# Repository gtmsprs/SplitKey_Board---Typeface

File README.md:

# PROJECT_TYPEFACE
Keyboard based on the designs by @koeg - https://stasis.hackclub.com/starter-projects/split-keyboard

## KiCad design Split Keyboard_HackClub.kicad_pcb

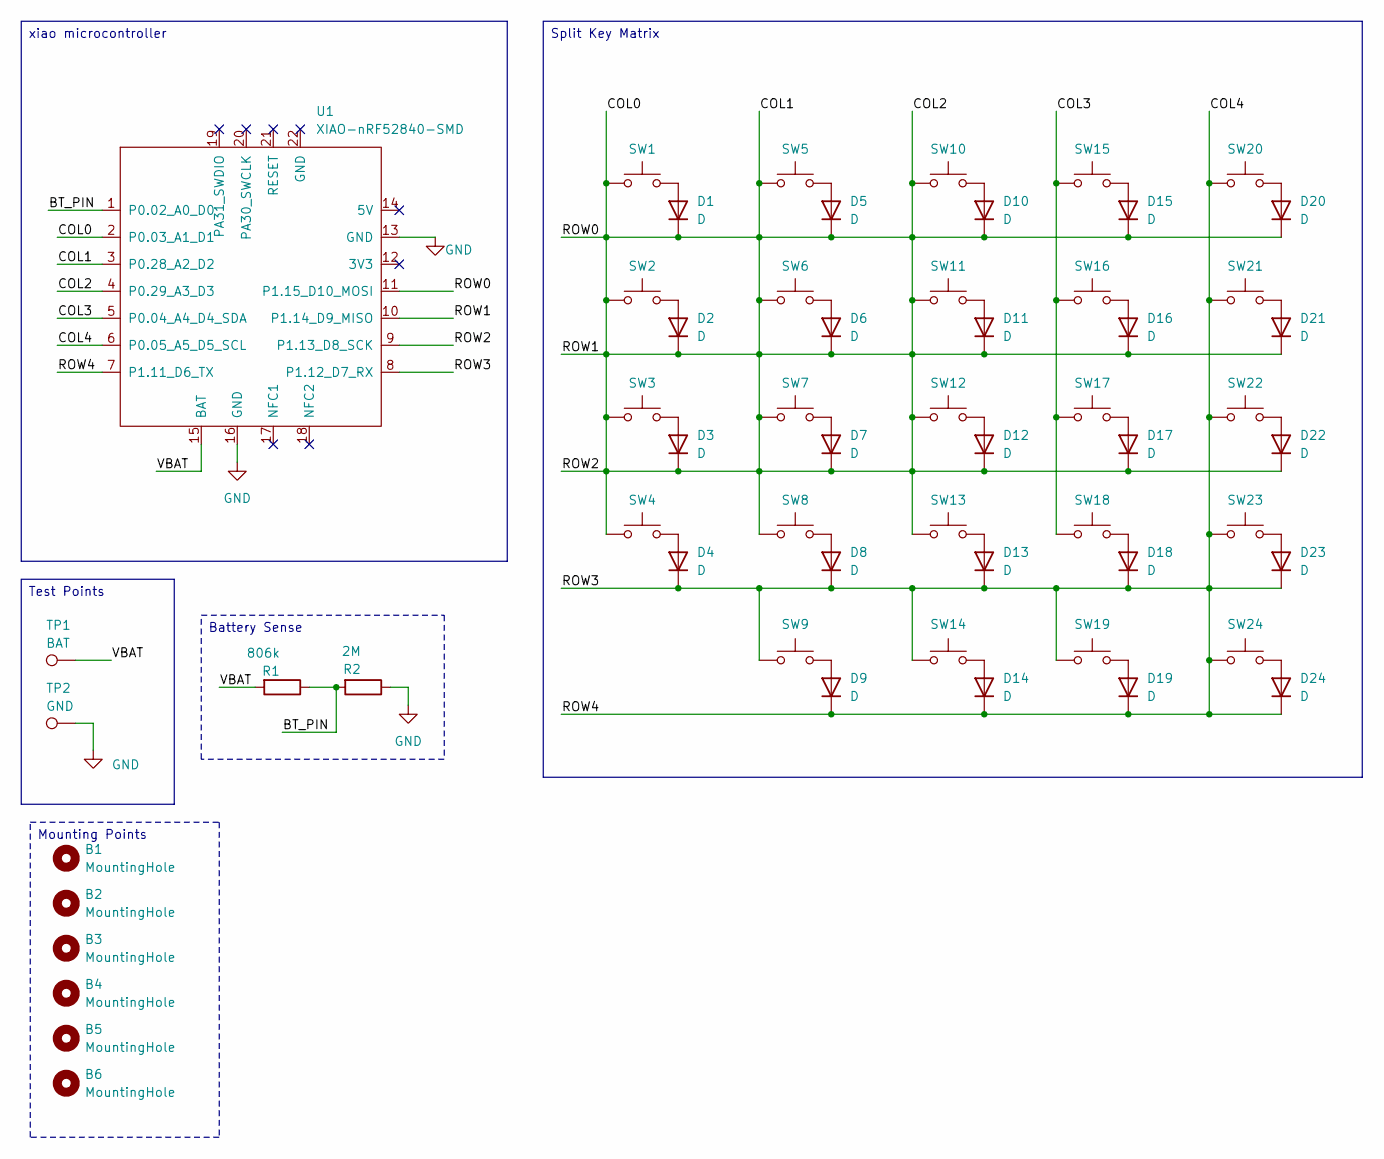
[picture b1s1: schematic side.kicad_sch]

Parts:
B1, B2, B3, B4, B5, B6: MountingHole
D1, D2, D3, D4, D5, D6, D7, D8, D9, D10, D11, D12, D13, D14, D15, D16, D17, D18, D19, D20, D21, D22, D23, D24: D; D_SMA
R1: 806k; R_0805_2012Metric
R2: 2M; R_0805_2012Metric
SW1, SW2, SW3, SW4, SW5, SW6, SW7, SW8, SW9, SW10, SW11, SW12, SW13, SW14, SW15, SW16, SW17, SW18, SW19, SW20, SW21, SW22, SW23, SW24: SW_Push; SW_KS33_HS_KS-2P02B01-02_HS_1u
TP1: BAT; TestPoint_Pad_D2.0mm
TP2: GND; TestPoint_Pad_D2.0mm
U1: XIAO-nRF52840-SMD; MCU_Seeed_ESP32C3

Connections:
/lefty/BT_PIN: R1.1, R2.2, U1.1 (P0.02_A0_D0)
/lefty/COL0: D1.1 (K), D2.1 (K), D3.1 (K), D5.1 (K), D6.1 (K), D7.1 (K), D10.1 (K), D11.1 (K), D12.1 (K), D15.1 (K), D16.1 (K), D17.1 (K), D20.1 (K), D21.1 (K), D22.1 (K), SW1.1, SW2.1, SW3.1, SW4.1, SW5.1, SW6.1, SW7.1, SW8.1, SW10.1, SW11.1, SW12.1, SW13.1, U1.2 (P0.03_A1_D1), U1.3 (P0.28_A2_D2), U1.4 (P0.29_A3_D3), U1.9 (P1.13_D8_SCK), U1.10 (P1.14_D9_MISO), U1.11 (P1.15_D10_MOSI)
/lefty/COL3: SW15.1, SW16.1, SW17.1, SW18.1, U1.5 (P0.04_A4_D4_SDA)
/lefty/COL4: D4.1 (K), D8.1 (K), D9.1 (K), D13.1 (K), D14.1 (K), D18.1 (K), D19.1 (K), D23.1 (K), D24.1 (K), SW9.1, SW14.1, SW19.1, SW20.1, SW21.1, SW22.1, SW23.1, SW24.1, U1.6 (P0.05_A5_D5_SCL), U1.7 (P1.11_D6_TX), U1.8 (P1.12_D7_RX)
/lefty/VBAT: R1.2, TP1.1 (1_1), U1.15 (BAT)
GND: R2.1, TP2.1 (1_1), U1.13 (GND), U1.16 (GND); also elsewhere on the board
unnamed: D1.2 (A), SW1.2
unnamed: D2.2 (A), SW2.2
unnamed: D3.2 (A), SW3.2
unnamed: D4.2 (A), SW4.2
unnamed: D5.2 (A), SW5.2
unnamed: D6.2 (A), SW6.2
unnamed: D7.2 (A), SW7.2
unnamed: D8.2 (A), SW8.2
unnamed: D9.2 (A), SW9.2
unnamed: D10.2 (A), SW10.2
unnamed: D11.2 (A), SW11.2
unnamed: D12.2 (A), SW12.2
unnamed: D13.2 (A), SW13.2
unnamed: D14.2 (A), SW14.2
unnamed: D15.2 (A), SW15.2
unnamed: D16.2 (A), SW16.2
unnamed: D17.2 (A), SW17.2
unnamed: D18.2 (A), SW18.2
unnamed: D19.2 (A), SW19.2
unnamed: D20.2 (A), SW20.2
unnamed: D21.2 (A), SW21.2
unnamed: D22.2 (A), SW22.2
unnamed: D23.2 (A), SW23.2
unnamed: D24.2 (A), SW24.2

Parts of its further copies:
D25, D26, D27, D28, D29, D30, D31, D32, D33, D34, D35, D36, D37, D38, D39, D40, D41, D42, D43, D44, D45, D46, D47, D48: D; D_SMA
R3: 806k; R_0805_2012Metric
R4: 2M; R_0805_2012Metric
SW25, SW26, SW27, SW28, SW29, SW30, SW31, SW32, SW33, SW34, SW35, SW36, SW37, SW38, SW39, SW40, SW41, SW42, SW43, SW44, SW45, SW46, SW47, SW48: SW_Push; SW_KS33_HS_KS-2P02B01-02_HS_1u
TP3: BAT; TestPoint_Pad_D2.0mm
TP4: GND; TestPoint_Pad_D2.0mm
U2: XIAO-nRF52840-SMD; MCU_Seeed_ESP32C3

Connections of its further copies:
/righty/BT_PIN: R3.1, R4.2, U2.1 (P0.02_A0_D0)
/righty/COL0: D25.1 (K), D26.1 (K), D27.1 (K), D29.1 (K), D30.1 (K), D31.1 (K), D34.1 (K), D35.1 (K), D36.1 (K), D39.1 (K), D40.1 (K), D41.1 (K), D44.1 (K), D45.1 (K), D46.1 (K), SW25.1, SW26.1, SW27.1, SW28.1, SW29.1, SW30.1, SW31.1, SW32.1, SW34.1, SW35.1, SW36.1, SW37.1, U2.2 (P0.03_A1_D1), U2.3 (P0.28_A2_D2), U2.4 (P0.29_A3_D3), U2.9 (P1.13_D8_SCK), U2.10 (P1.14_D9_MISO), U2.11 (P1.15_D10_MOSI)
/righty/COL3: SW39.1, SW40.1, SW41.1, SW42.1, U2.5 (P0.04_A4_D4_SDA)
/righty/COL4: D28.1 (K), D32.1 (K), D33.1 (K), D37.1 (K), D38.1 (K), D42.1 (K), D43.1 (K), D47.1 (K), D48.1 (K), SW33.1, SW38.1, SW43.1, SW44.1, SW45.1, SW46.1, SW47.1, SW48.1, U2.6 (P0.05_A5_D5_SCL), U2.7 (P1.11_D6_TX), U2.8 (P1.12_D7_RX)
/righty/VBAT: R3.2, TP3.1 (1_1), U2.15 (BAT)
GND: R4.1, TP4.1 (1_1), U2.13 (GND), U2.16 (GND); also elsewhere on the board
unnamed: D25.2 (A), SW25.2
unnamed: D26.2 (A), SW26.2
unnamed: D27.2 (A), SW27.2
unnamed: D28.2 (A), SW28.2
unnamed: D29.2 (A), SW29.2
unnamed: D30.2 (A), SW30.2
unnamed: D31.2 (A), SW31.2
unnamed: D32.2 (A), SW32.2
unnamed: D33.2 (A), SW33.2
unnamed: D34.2 (A), SW34.2
unnamed: D35.2 (A), SW35.2
unnamed: D36.2 (A), SW36.2
unnamed: D37.2 (A), SW37.2
unnamed: D38.2 (A), SW38.2
unnamed: D39.2 (A), SW39.2
unnamed: D40.2 (A), SW40.2
unnamed: D41.2 (A), SW41.2
unnamed: D42.2 (A), SW42.2
unnamed: D43.2 (A), SW43.2
unnamed: D44.2 (A), SW44.2
unnamed: D45.2 (A), SW45.2
unnamed: D46.2 (A), SW46.2
unnamed: D47.2 (A), SW47.2
unnamed: D48.2 (A), SW48.2

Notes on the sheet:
xiao microcontroller
Mounting Points
Battery Sense
Split Key Matrix
Test Points

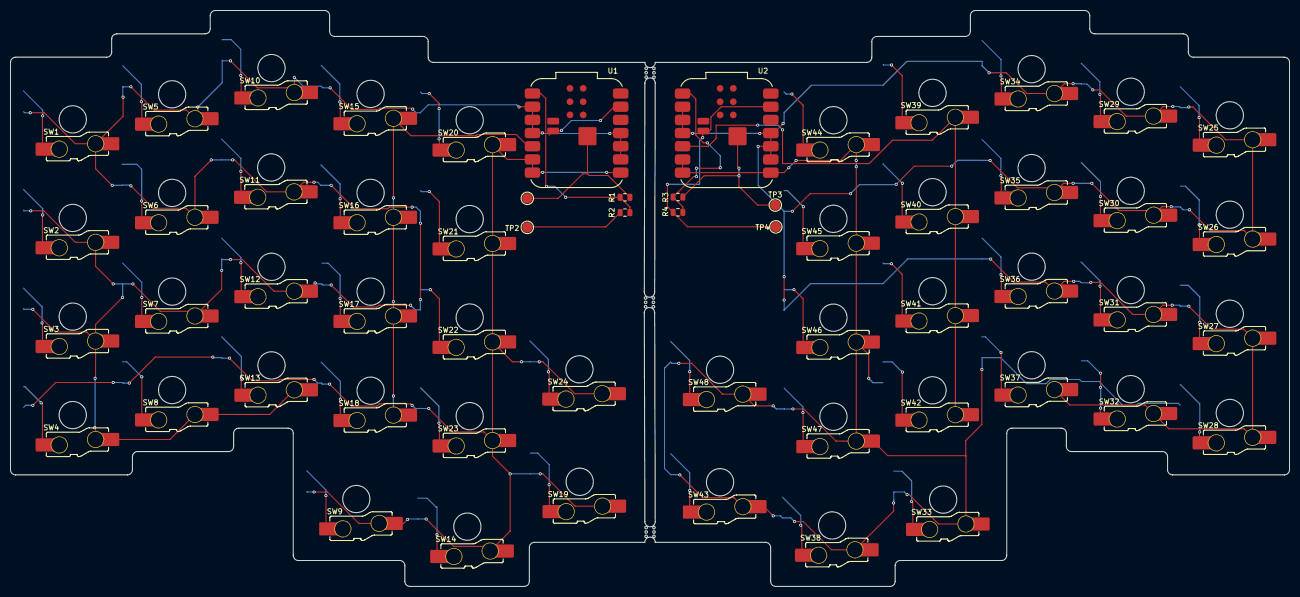
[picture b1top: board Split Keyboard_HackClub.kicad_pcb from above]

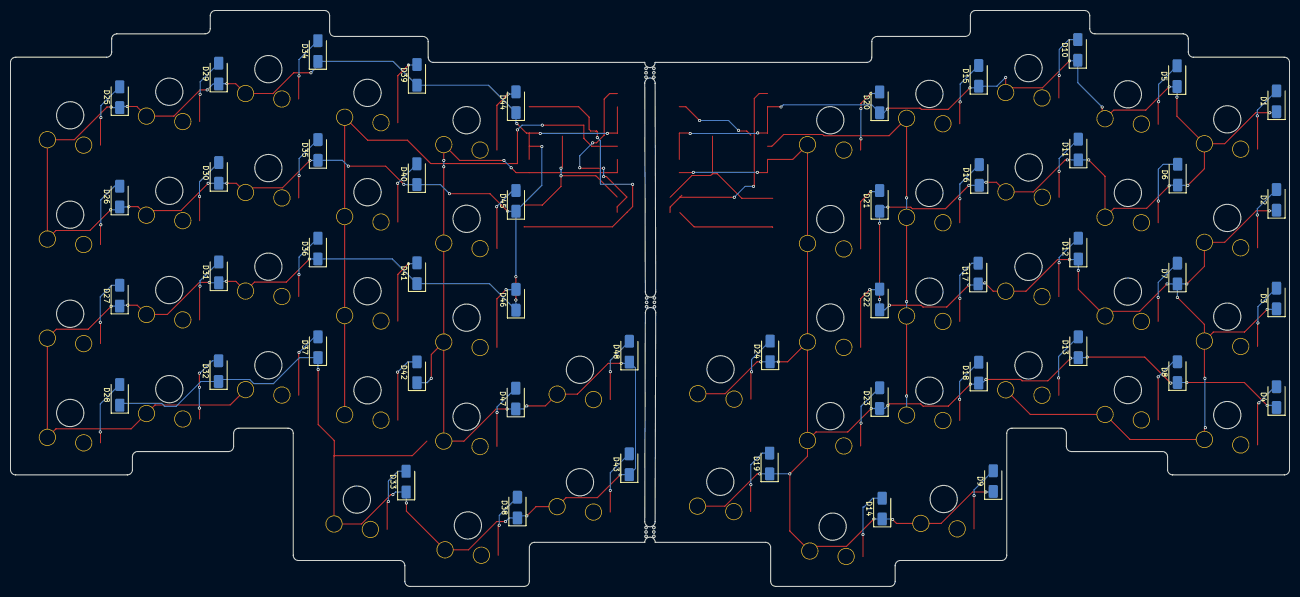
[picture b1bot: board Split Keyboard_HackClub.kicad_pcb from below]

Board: 2 copper layers, 246.4 x 110.9 mm, 106 parts (48 on the bottom side), 59 nets.
